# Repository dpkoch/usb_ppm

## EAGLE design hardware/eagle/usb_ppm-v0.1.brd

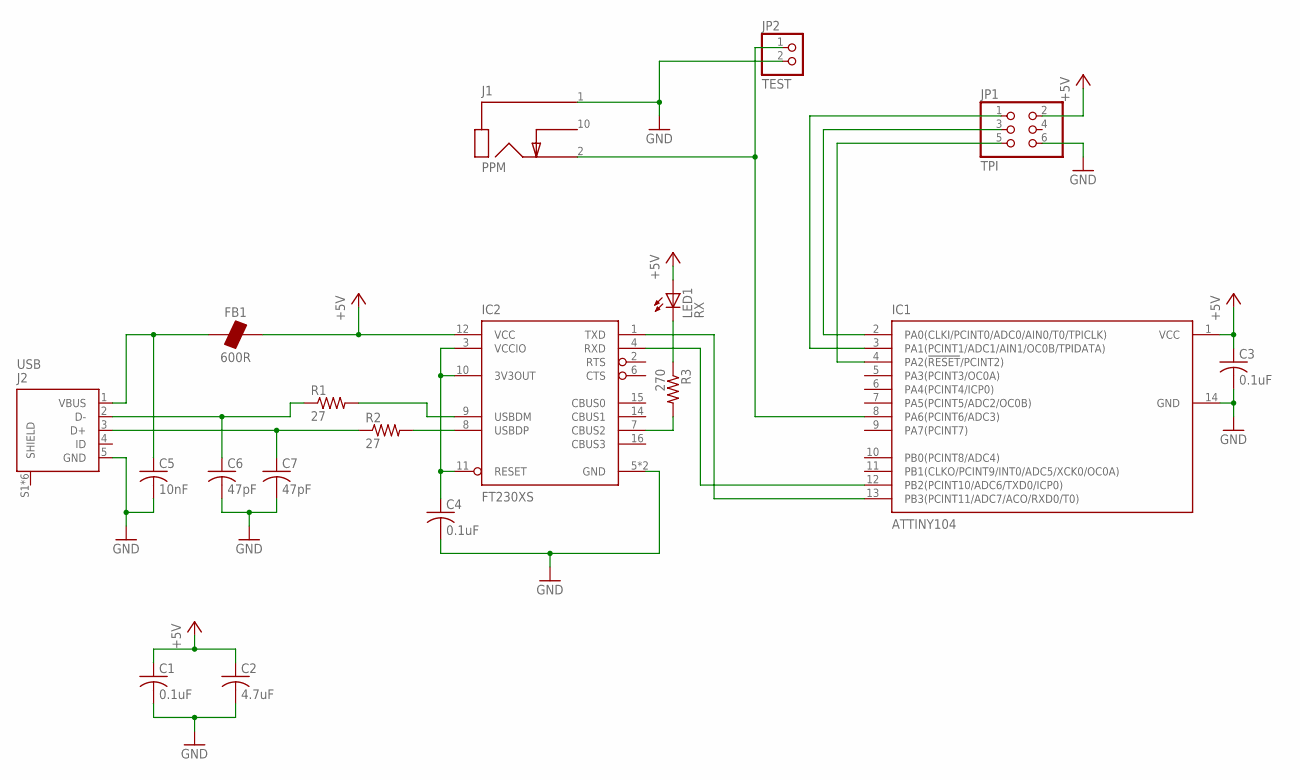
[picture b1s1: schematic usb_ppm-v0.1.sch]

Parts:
C1, C3, C4: 0.1uF; C0603
C2: 4.7uF; C0603
C5: 10nF; C0603
C6, C7: 47pF; C0603
FB1: 600R; 0603
IC1: ATTINY104; SOIC-14
IC2: FT230XS; SSOP-16
J1: PPM; MJ-3523-SMT
J2: USB; USB-MICRO-B-SMD
JP1: TPI; 2X03
JP2: TEST; 1X02
LED1: RX; CHIP-LED0603
R1, R2: 27; R0603
R3: 270; R0603

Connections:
3V3OUT: C4.1, IC2.3 (VCCIO), IC2.10 (3V3OUT), IC2.11 (RESET)
+5V: C1.1, C2.1, C3.1, FB1.2, IC1.1 (VCC), IC2.12 (VCC), JP1.2, LED1.A
GND: C1.2, C2.2, C3.2, C4.2, C5.2, C6.2, C7.2, IC1.14 (GND), IC2.5 (GND), IC2.13 (GND), J1.1 (SLEEVE), J2.5 (GND), JP1.6, JP2.2
unnamed: IC1.13 (PB3(PCINT11/ADC7/ACO/RXD0/T0)), IC2.1 (TXD)
unnamed: IC1.12 (PB2(PCINT10/ADC6/TXD0/ICP0)), IC2.4 (RXD)
unnamed: IC1.8 (PA6(PCINT6/ADC3)), J1.2 (TIP), JP2.1
unnamed: C5.1, FB1.1, J2.1 (VBUS)
unnamed: LED1.C, R3.1
unnamed: C6.1, J2.2 (D-), R1.1
unnamed: C7.1, J2.3 (D+), R2.1
unnamed: IC2.9 (USBDM), R1.2
unnamed: IC2.8 (USBDP), R2.2
unnamed: IC2.7 (CBUS2), R3.2
unnamed: IC1.3 (PA1(PCINT1/ADC1/AIN1/OC0B/TPIDATA)), JP1.1
unnamed: IC1.2 (PA0(CLKI/PCINT0/ADC0/AIN0/T0/TPICLK)), JP1.3
unnamed: IC1.4 (PA2(!RESET!/PCINT2)), JP1.5

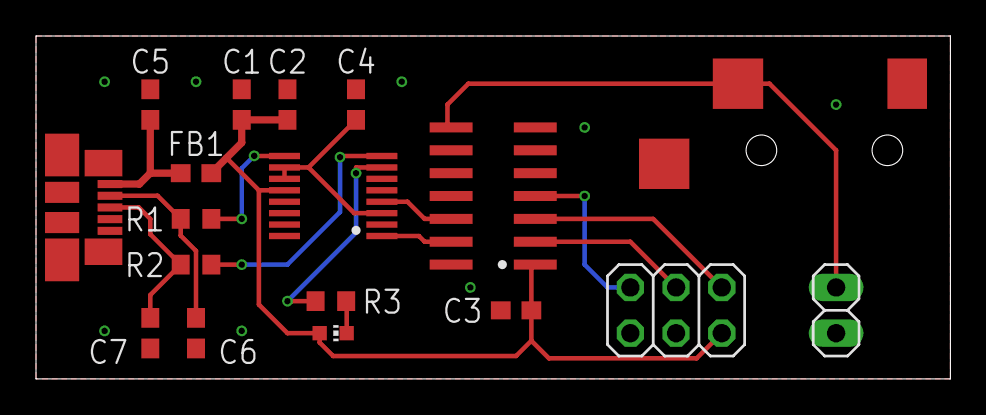
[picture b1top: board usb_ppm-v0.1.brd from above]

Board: 2 copper layers, 50.8 x 19.1 mm, 18 parts (0 on the bottom side), 16 nets.

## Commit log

2019-10-26 Commit existing hardware files
